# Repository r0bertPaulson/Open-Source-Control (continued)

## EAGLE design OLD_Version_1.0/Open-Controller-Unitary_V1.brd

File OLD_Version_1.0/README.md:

DO NOT USE THIS DESIGN. PROTOTYPE HAS NOT BEEN MADE OR TESTED. FOR REFERENCE ONLY. 

Please Use Version 2.1+

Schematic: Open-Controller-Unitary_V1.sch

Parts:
C1, C2: DNI; C0603
C3, C6, C9, C10, C14, C15, C17, C18, C19, C20, C22, C79, C93, C97: 0.1uF, 6.3V; C0402
C4: 330pF, DNI; C0805
C7, C12: 18pF, 50V; C0402
C8: 1nF; C0402
C11: 220uF, 6.3V; B/3528-21R
C13: 2.2uF, 6.3V; C0402
C16, C21: 10uF, 10V; C0805
C41, C44: 10uF, 16V; C0805
C42, C43, C45: 0.1uF, 16V; C0402
C46, C95, C96: 4.7uF; 1206
C85, C87, C88: 2200pF, 6.3V; C0402
C94: 1mF; CPOL-RADIAL-5MM-10MM
C111, C121, C131, C141, C151, C161: 1uF; C0805
D1, D2, D9, D21, D22, D23, D24, D25: LTST-C191KFKT; EIA-STD
D3: S1D; SMA
D4, D5, D6, D7, D8: LTST-C191KGKT; EIA-STD
D10, D11: SMBJ7.0CA; SMBJ
D13: B550C-13-F; SMC
D14, D15: SMBJ12CA; SMBJ
D16, D17: MBR0520LT; SOD123
EC30, EC31, EC34: 0.1uF, 6.3V; C0402
EC32: 10uF, 10V; C0805
EC33: 1uF, 10V; C0402
EC35: 470pF, 6.3V; C0402
EC36, EC37, EC38, EC39: 15pF, DNI; C0402
EC40: 0.022uF, 10V; C0402
EC41, EC42: 30pF, 50V; C0402
ER98, ER99, ER100, ER105: 1.5K, 1%; R0402
ER101, ER102, ER103, ER104, ER120, ER129: 10K, 1%; R0402
ER106, ER107, ER108, ER109: 49.9, 1%; R0402
ER110, ER111, ER112, ER113, ER114, ER116, ER118, ER119, ER123, ER124: 100, 1%; R0402
ER115, ER117: 470, 1%; R0402
ER122, ER126: 0, 1%; R0402
ER125: 1M, 1%, DNI; R0402
ER127: 10, 1%; R0402
ER128: 12.1K, 1%; R0402
F1: 4A Fuse; F1206W
F3, F4: MICROSMD010F-2; FUS_MICROSMD010F_TYCO
FB7: 150ohm, 800mA; C0805
FUD1, FUD2, FUD3, FUD4, FUD5, FUD6: FIDUCIAL; FIDUCIAL_40MIL
G1: CR2032V
IC1: LM2596S; TO263-5
IC2: ULN2003AD; SO16
IC3: L7824CT; 78XXL
IC4, IC5: 74HC165D; SO16
J1, J2, J6, J11, J12, J13, J21, J22, J23, J31, J32, J33, J41, J42, J43, J51, J52, J53, J61, J62, J63: 826646-2; H2-2.54
J3: 6p-2.54; H6-2.54
J4: CTI-JTAG
J7, J8: TH-2X5; H2X5-2.54
K1, K2, K3, K4, K5: JS1-24V-F; JS-M
L2: MSS1260
L3: 78253/55MVC-R; IND_78253_MC
MGT1, MGT2, MGT3, MGT4: MOUNTING_HOLE
Q1: MMBT2907; SOT23-BEC
R1, R3, R20, R42, R43, R44, R45, R46, R47, R48, R49, R50, R51, R52, R86, R87, R88, R89, R90, R91, R92, R160, R161, R171, R172, R173, R174, R175, R281, R282, R283, R284, R285, R286, R287, R288, R291, R292, R293, R294: 10K, 1%; R0402
R2, R9, R12, R13, R24, R26, R35, R36, R37, R38, R95, R96: 1.5K, 1%; R0402
R4, R5, R11, R19, R25, R28, R29, R30, R33: 0, 1%; R0402
R6, R54, R64, R65, R66, R70, R72, R73, R74, R75, R76, R77, R78, R79, R80, R84, R85: 100K, 1%, DNI; R0402
R8: 1K, 1%; R0402
R10: 0, 1%; R0805
R15: 40.2K, 1%; R0402
R17: 1.00K, 1%; R0805
R18, R22, R39, R40, R41: 4.75K, 1%; R0402
R21: 499; R0402
R27, R53, R55, R56, R57, R58, R59, R60, R61, R62, R63, R67, R68, R71, R81, R82, R83, R158: 100K, 1%; R0402
R31: 22, 1%; R0402
R32: 1M, 1%; R0402
R34: .1, 0805; R0805
R69: 100, 1%; R0402
R93: 3.09K, 1%; R0805
R94: 100, 5% DNI; R0805
R181, R182, R183, R184, R185, R186: 47V 200A; CT/CN1206
R211, R221, R231, R241, R251, R261: 80, 0.1%; 0309/12
R212, R214, R222, R224, R232, R234, R242, R244, R252, R254, R262, R264: 10K, 1%; R0805
R213, R223, R233, R243, R253, R263: 2K, 1%; R0805
RTC1: DS3231M; SO08
S1, S2: KMR231GLFS; SW4SMD_63X161LS
S11, S12: P101
S13: DS04; DS-04
TP1, TP2, TP3, TP4, TP12, TP13, TP14, TP15, TP16, TP21, TP22, TP23, TP24, TP27, TP28, TP29, TP30: TPB0,65; TP_B0,65
TP5, TP6, TP7, TP8, TP9, TP10, TP26: TESTPAD/W_HOLE_1X1
U1: OSD3358-512M-BSM; OSD335X-BGA-256
U2: TPD4S012_DRY_6_P1_M; DRY6
U3: SN74LVC1G07_DCK_5; DCK5
U4: APX811SOT; SOT143-R
U5: TLVH431; SOT23-3
U6: SN74LVC2G241_DCU_8; DCU8
U7: EMMC04G-S100-B08U; MICRON_EMMC_153
U8: LAN8710; LAN8710A-QFN32
U16: AT97SC3205T-G3M4400B; QFN32-0.4-4X4MM
U21: S25FL127S; W-PDFN-8
U25: ISO3086TDW; DW16
U26: LP2985A-33DBVR; DBV5
U27: TCAN1051HV; BEAGLEBONE_BLUE_D8
U$3, U$5, U$6: MCP6002SMT; SOIC8
U$4: MCP6001; SOT23-5
X1: 10118192-0001LF; 10118192-0001LF(MICRO-USB-B-AMPHENOL-FCI)
X2: MC2
X3: DM3BT-DSF-PEJS
X4: J0011D01BNL; SI-50170
X7: MSTBA2
X8: MC10
X9, X10, X11: MC4
X12: MC3
X13: MSTBA3
Y2: 7A-24.000MAAJ-T; CRYSTAL-TXC-7A
Y7: 7A-25.000MAAE-T; CRYSTAL-TXC-7A

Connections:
1P8V_REF: R212.2, R222.2, R232.2, R242.2, R252.2, R262.2, U$3.8 (V+), U$4.1 (OUT), U$4.4 (-IN), U$5.8 (V+), U$6.8 (V+)
5V_OUT: D13.C, IC1.2 (OUT), L2.1
24VAC: D3.A, F1.2
24VAC_IN: F1.1, X7.1
24VAC_UNREG: C94.+, C95.1, D3.C, IC1.1 (IN), IC3.IN
24VDC_AUX: D2.1 (A), D21.1 (A), D22.1 (A), D23.1 (A), D24.1 (A), D25.1 (A), IC2.9 (CD+), IC3.OUT, K1.1, K2.1, K3.1, K4.1, K5.1, X2.1, X2.2
AGND: C8.2, C9.2, C10.2, C111.2, C121.2, C131.2, C141.2, C151.2, C161.2, R25.2, R211.1, R213.2, R221.1, R223.2, R231.1, R233.2, R241.1, R243.2, R251.1, R253.2, R261.1, R263.2, U1.A9 (AGND_ADC), U$3.4 (V-), U$4.2 (V-), U$5.4 (V-), U$6.4 (V-), X9.2, X9.4, X10.2, X10.4, X11.2, X11.4
AIN0: U1.A8 (AIN0)
AIN1: U1.B8 (AIN1), U$3.1 (OUT), U$3.2 (-IN)
AIN2: U1.B6 (AIN2), U$3.6 (-IN), U$3.7 (OUT)
AIN3: U1.C6 (AIN3), U$5.1 (OUT), U$5.2 (-IN)
AIN4: U1.C7 (AIN4), U$5.6 (-IN), U$5.7 (OUT)
AIN5: U1.C8 (AIN5), U$6.1 (OUT), U$6.2 (-IN)
AIN6: U1.C9 (AIN6), U$6.6 (-IN), U$6.7 (OUT)
AIN7: U1.D6 (PMIC_MUX_OUT), U1.D7 (AIN7)
B03_NO: K3.NO (S), X8.6
BAT_SENSE: TP6.P$1, U1.N7 (PMIC_BAT_SENSE)
BO1_C: K1.C, X8.9
BO1_NO: K1.NO (S), X8.10
BO2_C: K2.C, X8.7
BO2_NO: K2.NO (S), X8.8
BO3_C: K3.C, X8.5
BO4_C: K4.C, X8.3
BO4_NO: K4.NO (S), X8.4
BO5_C: K5.C, X8.1
BO5_NO: K5.NO (S), X8.2
B_UART0_RX: J3.4, R27.2, U6.2 (1A)
B_UART0_TX: J3.5, U6.3 (2Y)
CGND: D10.A, D11.A, MGT1.P$1, MGT2.P$1, MGT3.P$1, MGT4.P$1, R34.2, R181.2, R182.2, R183.2, R184.2, R185.2, R186.2, X1.CGND1 (SGND1), X1.CGND2 (SGND2), X1.CGND3 (SGND3), X1.CGND4 (SGND4), X1.CGND5 (SGND5), X1.CGND6 (SGND6), X3.CGND1, X3.CGND2, X3.CGND3, X3.CGND4, X3.CGND5, X3.CGND6, X4.S1 (SHD1), X4.S2 (SHD2), X12.1
CLKOUT2: C2.2, J4.18 (EMU3), U1.B4 (XDMA_EVENT_INTR1)
CRS: ER124.1, U8.14 (CRS)
EEPROM_WP: J1.1, U1.M2 (EEPROM_WP)
EHRPWM1A: U1.P12 (GPMC_A2)
EHRPWM1B: U1.T13 (GPMC_A3)
EHRPWM2A: U1.T4 (GPMC_AD8)
EHRPWM2B: U1.P5 (GPMC_AD9)
EMMC_RSTN: R19.2, R52.1, U7.K5 (RST#)
EMMC_VCCI: C13.2, U7.C2 (VDDI)
GND: C1.1, C2.1, C3.2, C6.1, C11.-, C13.1, C14.2, C15.2, C16.1, C17.1, C18.1, C19.1, C20.1, C21.2, C22.2, C41.2, C42.2, C79.2, C85.2, C87.2, C88.2, C93.2, C94.-, C95.2, C96.2, C97.2, D13.A, EC30.2, EC31.2, EC32.2, EC33.2, EC34.2, EC35.2, EC36.2, EC37.2, EC38.2, EC39.2, EC40.2, EC41.2, EC42.2, ER101.2, ER102.2, ER103.2, ER104.2, ER115.1, ER117.1, ER120.1, ER128.1, ER129.2, G1.-, IC1.3 (GND), IC1.5 (EN), IC1.6 (GND), IC2.8 (GND), IC3.GND, IC4.8 (GND), IC4.15 (INH), IC5.3 (E), IC5.4 (F), IC5.5 (G), IC5.6 (H), IC5.8 (GND), IC5.15 (INH), J1.2, J2.2, J3.1, J4.4 (TDIS), J4.8 (GND1), J4.10 (GND2), J4.12 (GND3), J4.16 (GND4), J4.20 (GND5), J6.2, R1.2, R2.2, R3.2, R6.1, R9.2, R17.1, R18.1, R26.2, R27.1, R34.1, R35.2, R36.2, R37.2, R38.2, R39.1, R53.1, R54.1, R55.1, R56.1, R57.1, R58.1, R59.1, R60.1, R61.1, R62.1, R63.1, R64.1, R65.1, R66.1, R67.1, R68.1, R158.2, R281.1, R282.1, R283.1, R284.1, R285.1, R286.1, R287.1, R288.1, R291.1, R292.1, R293.1, R294.1, S1.2, S1.4, S2.1, S2.3, TP8.P$1, U1.D8 (DGND), U1.D9 (DGND), U1.E5 (DGND), U1.E6 (DGND), U1.E7 (DGND), U1.E8 (DGND), U1.E9 (DGND), U1.E10 (DGND), U1.E11 (DGND), U1.E12 (DGND), U1.F5 (DGND), U1.F12 (DGND), U1.G5 (DGND), U1.G12 (DGND), U1.H4 (DGND), U1.H5 (DGND), U1.H12 (DGND), U1.H13 (DGND), U1.J4 (DGND), U1.J5 (DGND), U1.J12 (DGND), U1.J13 (DGND), U1.K5 (DGND), U1.K12 (DGND), U1.L5 (DGND), U1.L12 (DGND), U1.M5 (DGND), U1.M6 (DGND), U1.M7 (DGND), U1.M8 (DGND), U1.M9 (DGND), U1.M10 (DGND), U1.M11 (DGND), U1.M12 (DGND), U1.N8 (DGND), U1.N9 (DGND), U2.4 (GND), U3.3 (GND), U4.1 (GND), U6.1 (*1OE), U6.4 (GND), U7.C4 (VSSQ1), U7.E7 (VSS1), U7.G5 (VSS2), U7.H10 (VSS3), U7.K8 (VSS4), U7.N2 (VSSQ2), U7.N5 (VSSQ3), U7.P4 (VSSQ4), U7.P6 (VSSQ5), U8.33 (GND_EP), U16.2 (GND), U16.5 (TESTL), U16.6 (XTAMPER), U16.9 (GND), U16.18 (PIRQ#), U16.19 (ATEST), U16.20 (TWI_WAKEUP#), U16.21 (ATEST), U16.23 (GND), U16.24 (ATEST), U16.32 (GND), U21.4 (VSS), U25.3 (GND1), U27.2 (GND), X1.GND, X3.6 (VSS), X3.GND, X4.8 (D_GND), X7.2
GPIO0_18: RTC1.3 (SQW), U1.J15 (USB0_DRVVBUS)
GPIO0_26: U1.R5 (GPMC_AD10)
GPIO0_27: U1.T5 (GPMC_AD11)
GPIO1_12: IC2.2 (I2), U1.P6 (GPMC_AD12)
GPIO1_13: IC2.3 (I3), U1.R6 (GPMC_AD13)
GPIO1_14: IC2.4 (I4), U1.T6 (GPMC_AD14)
GPIO1_15: IC2.5 (I5), U1.P7 (GPMC_AD15)
GPIO1_16: U1.T12 (GPMC_A0), U25.6 (!RE), U25.7 (DE)
GPIO1_28: U1.N14 (GPMC_BEN1)
GPIO1_29: U1.P3 (GPMC_CSN0)
GPIO2_1: U1.T7 (GPMC_CLK)
GPIO3_21: IC2.1 (I1), U1.C4 (MCASP0_AHCLKX)
HDMICLK_DISN: U1.T16 (GPMC_A11)
HDMI_INT: U1.T15 (GPMC_A9)
I2C0_SCL: R12.1, U1.C10 (I2C0_SCL), U1.D10 (PMIC_SCL), U16.29 (SM_CLK)
I2C0_SDA: R13.1, U1.C11 (I2C0_SDA), U1.D11 (PMIC_SDA), U16.30 (SM_DAT)
I2C2_SCL: R95.1, RTC1.8 (SCL), U1.A10 (UART1_RTSN)
I2C2_SDA: R96.1, RTC1.7 (SDA), U1.B10 (UART1_CTSN)
ISO_GND: C43.2, C44.2, C45.2, C46.2, D14.A, D15.A, L3.5, U25.9 (GND2_2), U25.15 (GND2), U26.2 (GND), X13.3
ISO_VIN: C44.1, C45.1, D16.C, D17.C, U26.1 (VIN), U26.3 (ON/!OFF)
JTAG_EMU0: J4.13 (EMU0), R40.1, U1.E2 (EMU0)
JTAG_EMU1: J4.14 (EMU1), R41.1, U1.E3 (EMU1)
JTAG_TCK: J4.9 (TCKRTN), J4.11 (TCK), U1.D1 (TCK)
JTAG_TDI: J4.3 (TDI), U1.C1 (TDI)
JTAG_TDO: J4.7 (TDO), U1.C2 (TDO)
JTAG_TMS: J4.1 (TMS), U1.D2 (TMS)
JTAG_TRSTN: J4.2 (TRSTN), R39.2, U1.D3 (TRSTN)
LCD_DATA0: J8.9, R68.2, R85.1, U1.G3 (LCD_DATA0)
LCD_DATA1: J8.10, R67.2, R84.1, U1.G2 (LCD_DATA1)
LCD_DATA2: J8.7, R66.2, R69.1, R83.1, U1.G1 (LCD_DATA2)
LCD_DATA3: J8.8, R65.2, R82.1, U1.H3 (LCD_DATA3)
LCD_DATA4: J8.5, R64.2, R81.1, U1.H2 (LCD_DATA4)
LCD_DATA5: J8.6, R63.2, R80.1, U1.H1 (LCD_DATA5)
LCD_DATA6: J8.3, R62.2, R79.1, U1.J3 (LCD_DATA6)
LCD_DATA7: J8.4, R61.2, R78.1, U1.J2 (LCD_DATA7)
LCD_DATA8: J8.1, R60.2, R77.1, U1.J1 (LCD_DATA8)
LCD_DATA9: J8.2, R59.2, R76.1, U1.K3 (LCD_DATA9)
LCD_DATA10: J7.10, R58.2, R75.1, U1.K2 (LCD_DATA10)
LCD_DATA11: J7.8, R57.2, R74.1, U1.K1 (LCD_DATA11)
LCD_DATA12: J7.9, R56.2, R73.1, U1.L3 (LCD_DATA12)
LCD_DATA13: J7.7, R55.2, R72.1, U1.L2 (LCD_DATA13)
LCD_DATA14: J7.5, R54.2, R71.1, U1.L1 (LCD_DATA14)
LCD_DATA15: J7.6, R53.2, R70.1, U1.M3 (LCD_DATA15)
LCD_DE: J7.4, R28.2
LCD_HSYNC: J7.3, R29.2
LCD_PCLK: J7.2, R31.2
LCD_VSYNC: J7.1, R30.2
LDO_PGOOD: TP22.TP, U1.N4 (PMIC_LDO_PGOOD), U1.N5 (RTC_PWRONRSTN)
MDIO_CLK: U1.D13 (MDC), U8.17 (MDC)
MDIO_DATA: ER105.2, U1.E13 (MDIO), U8.16 (MDIO)
MII1_COL: ER123.2, U1.F15 (MII1_COL)
MII1_CRS: ER124.2, U1.F14 (MII1_CRS)
MII1_RXCLK: ER116.2, U1.E16 (MII1_RX_CLK)
MII1_RXD0: ER113.2, U1.E14 (MII1_RXD0)
MII1_RXD1: ER112.2, U1.D16 (MII1_RXD1)
MII1_RXD2: ER111.2, U1.D15 (MII1_RXD2)
MII1_RXD3: ER110.2, U1.D14 (MII1_RXD3)
MII1_RXDV: ER114.2, U1.F16 (MII1_RX_DV)
MII1_RXERR: ER118.2, U1.E15 (MII1_RX_ER)
MII1_TXCLK: ER119.2, U1.H16 (MII1_TX_CLK)
MII1_TXD0: U1.H15 (MII1_TXD0), U8.22 (TXD0)
MII1_TXD1: U1.H14 (MII1_TXD1), U8.23 (TXD1)
MII1_TXD2: U1.G16 (MII1_TXD2), U8.24 (TXD2)
MII1_TXD3: U1.G15 (MII1_TXD3), U8.25 (TXD3)
MII1_TXEN: U1.G14 (MII1_TX_EN), U8.21 (TXEN)
MMC0_CD: J4.19 (EMU4), R92.1, U1.C14 (SPI0_CS1), X3.CD (CD#)
MMC0_CLK: R88.1, U1.B15 (MMC0_CLK), X3.5 (CLK)
MMC0_CMD: R87.1, U1.B16 (MMC0_CMD), X3.3 (CMD/DI)
MMC0_DAT0: R89.1, U1.A16 (MMC0_DAT0), X3.7 (DAT0/DO)
MMC0_DAT1: R90.1, U1.A15 (MMC0_DAT1), X3.8 (DAT1)
MMC0_DAT2: R86.1, U1.C16 (MMC0_DAT2), X3.1 (DAT2)
MMC0_DAT3: R91.1, U1.C15 (MMC0_DAT3), X3.2 (DAT3/CS)
MMC1_CLK: R51.1, U1.P2 (GPMC_CSN1), U7.M6 (CLK)
MMC1_CMD: R50.1, U1.P1 (GPMC_CSN2), U7.M5 (CMD)
MMC1_DAT0: R42.1, U1.R3 (GPMC_AD0), U7.A3 (DAT0)
MMC1_DAT1: R43.1, U1.R2 (GPMC_AD1), U7.A4 (DAT1)
MMC1_DAT2: R44.1, U1.R1 (GPMC_AD2), U7.A5 (DAT2)
MMC1_DAT3: R45.1, U1.T3 (GPMC_AD3), U7.B2 (DAT3)
MMC1_DAT4: R46.1, U1.T2 (GPMC_AD4), U7.B3 (DAT4)
MMC1_DAT5: R47.1, U1.T1 (GPMC_AD5), U7.B4 (DAT5)
MMC1_DAT6: R48.1, U1.P4 (GPMC_AD6), U7.B5 (DAT6)
MMC1_DAT7: R49.1, U1.R4 (GPMC_AD7), U7.B6 (DAT7)
MODE2: ER99.2, ER123.1, U8.15 (COL/CRS_DV/MODE2)
unnamed: R10.1, X1.VBUS
unnamed: D7.2 (C), R38.1
unnamed: J6.1, R69.2
unnamed: R8.2, U4.2 (RESET#)
unnamed: TP1.TP, U1.F4 (VDDS_DDR)
unnamed: D2.2 (C), R3.1
unnamed: D1.2 (C), R26.1
unnamed: R15.2, R20.1, U5.1 (REF)
unnamed: Q1.B, R21.1, U5.2 (CATHODE)
unnamed: D6.2 (C), R37.1
unnamed: D5.2 (C), R36.1
unnamed: J11.1, J12.1, R181.1, R214.1, X9.1
unnamed: D4.2 (C), R35.1
unnamed: D10.C, U27.7 (CANH), X12.3
unnamed: D11.C, U27.6 (CANL), X12.2
unnamed: TP2.TP, U1.G4 (VDD_CORE)
unnamed: TP3.TP, U1.F13 (VDD_MPU)
unnamed: TP4.TP, U1.G13 (VDDS_PLL)
unnamed: R4.1, U1.A4 (XDMA_EVENT_INTR0)
unnamed: R161.2, U21.3 (W#)
unnamed: J51.1, J52.1, R185.1, R254.1, X11.1
unnamed: R160.2, U21.7 (HOLD#)
unnamed: R19.1, U1.R13 (GPMC_A4)
unnamed: R11.1, S1.1, S1.3
unnamed: C151.1, J53.1, R254.2, U$6.3 (+IN)
unnamed: J51.2, R251.2
unnamed: R5.1, U3.4 (Y)
unnamed: J53.2, R253.1
unnamed: J52.2, R252.1
unnamed: R1.1, U1.M16 (RTC_KALDO_ENN)
unnamed: J61.1, J62.1, R186.1, R264.1, X11.3
unnamed: D8.2 (C), R2.1
unnamed: EC40.1, ER122.2, X4.4 (TCT), X4.5 (RCT)
unnamed: D21.2 (C), R171.1
unnamed: D23.2 (C), R173.1
unnamed: D22.2 (C), R172.1
unnamed: IC2.16 (O1), K1.2, R171.2
unnamed: IC2.15 (O2), K2.2, R172.2
unnamed: C161.1, J63.1, R264.2, U$6.5 (+IN)
unnamed: D24.2 (C), R174.1
unnamed: D25.2 (C), R175.1
unnamed: J11.2, R211.2
unnamed: J12.2, R212.1
unnamed: J61.2, R261.2
unnamed: J63.2, R263.1
unnamed: J62.2, R262.1
unnamed: IC2.13 (O4), K4.2, R174.2
unnamed: IC2.12 (O5), K5.2, R175.2
unnamed: IC2.14 (O3), K3.2, R173.2
unnamed: J13.2, R213.1
unnamed: J21.1, J22.1, R182.1, R224.1, X9.3
unnamed: C121.1, J23.1, R224.2, U$3.5 (+IN)
unnamed: G1.+, RTC1.6 (VBAT)
unnamed: IC4.6 (H), R288.2, S12.8
unnamed: C111.1, J13.1, R214.2, U$3.3 (+IN)
unnamed: J21.2, R221.2
unnamed: J23.2, R223.1
unnamed: J22.2, R222.1
unnamed: D9.2 (C), R9.1
unnamed: C4.1, R94.1
unnamed: J31.1, J32.1, R183.1, R234.1, X10.1
unnamed: C131.1, J33.1, R234.2, U$5.3 (+IN)
unnamed: J31.2, R231.2
unnamed: J33.2, R233.1
unnamed: R31.1, U1.F1 (LCD_PCLK)
unnamed: J32.2, R232.1
unnamed: R30.1, U1.F3 (LCD_VSYNC)
unnamed: J41.1, J42.1, R184.1, R244.1, X10.3
unnamed: C141.1, J43.1, R244.2, U$5.5 (+IN)
unnamed: J41.2, R241.2
unnamed: J43.2, R243.1
unnamed: C4.2, IC1.4 (FB), R17.2, R93.1
unnamed: J42.2, R242.1
unnamed: D14.C, F3.2, U25.11 (Y), U25.14 (A)
unnamed: D15.C, F4.2, U25.12 (Z), U25.13 (B)
unnamed: F3.1, X13.1
unnamed: F4.1, X13.2
unnamed: R29.1, U1.F2 (LCD_HSYNC)
unnamed: C43.1, C46.1, U25.16 (VCC2), U26.5 (VOUT)
unnamed: R28.1, U1.E1 (LCD_AC_BIAS_EN)
unnamed: D16.A, L3.6
unnamed: D17.A, L3.4
unnamed: L3.1, U25.1 (D1)
unnamed: L3.3, U25.2 (D2)
unnamed: IC4.5 (G), R287.2, S12.4
unnamed: IC4.4 (F), R286.2, S12.2
unnamed: IC4.3 (E), R285.2, S12.1
unnamed: IC4.14 (D), R284.2, S11.8
unnamed: IC4.13 (C), R283.2, S11.4
unnamed: IC4.12 (B), R282.2, S11.2
unnamed: IC4.11 (A), R281.2, S11.1
unnamed: IC5.11 (A), R291.2, S13.8
unnamed: IC5.12 (B), R292.2, S13.7
unnamed: IC5.13 (C), R293.2, S13.6
unnamed: IC5.14 (D), R294.2, S13.5
unnamed: IC4.10 (SER), IC5.9 (QH)
unnamed: ER126.1, U8.5 (XTAL1/CLKIN)
unnamed: EC42.1, ER125.2, ER126.2, Y7.P$2 (2)
unnamed: EC41.1, ER127.2, Y7.P$1 (1)
unnamed: ER125.1, ER127.1, U8.4 (XTAL2)
unnamed: ER128.2, U8.32 (RBIAS)
unnamed: ER129.1, U8.18 (NINT/TXER/TXD4)
unnamed: ER120.2, U8.2 (LED2/!INTSEL), X4.A1 (YELA)
unnamed: U8.3 (LED1/REGOFF), X4.C2 (GRNA)
unnamed: EC33.1, EC35.1, U8.6 (VDDCR)
unnamed: ER115.2, X4.C1 (YELC)
unnamed: ER117.2, X4.A2 (GRNC)
OSC0_GND: C7.2, C12.2, U1.N15 (OSC0_GND)
OSC0_IN: C12.1, R32.2, U1.P16 (OSC0_IN), Y2.P$2 (2)
OSC0_OUT: C7.1, R32.1, U1.N16 (OSC0_OUT), Y2.P$1 (1)
OSC1_GND: RTC1.5 (GND), U1.B5 (OSC1_GND)
OSC1_IN: R24.2, RTC1.1 (32KHZ), U1.A6 (OSC1_IN)
OSC1_OUT: U1.A5 (OSC1_OUT)
PMIC_INT: TP24.TP, U1.D4 (EXTINTN), U1.E4 (PMIC_NINT)
PMIC_MUX_IN: R18.2, R22.1, U1.N13 (PMIC_MUX_IN)
PMIC_NRESET: J2.1, U1.M13 (PMIC_NRESET)
PMIC_NWAKEUP: TP23.TP, U1.L4 (PMIC_NWAKEUP), U1.M4 (EXT_WAKEUP)
PMIC_PGOOD: U1.N12 (PMIC_PGOOD), U1.P11 (PWRONRSTN), U3.2 (A)
PWR_BUT: S2.2, S2.4, U1.T11 (PMIC_PB_IN)
PWR_EN: TP21.TP, U1.N10 (PMIC_POWER_EN), U1.N11 (PMIC_PWR_EN)
RESET: R5.2, R11.2, U4.3 (MR#)
RTC_RST: RTC1.4 (RST), U1.R12 (GPMC_A1)
RXD0: ER98.2, ER113.1, U8.11 (RXD0/MODE0)
RXD1: ER100.2, ER112.1, U8.10 (RXD1/MODE1)
RXD2: ER103.1, ER111.1, U8.9 (RXD2/RMIISEL)
RXD3: ER102.1, ER110.1, U8.8 (RXD3/PHYAD2)
RX_CLK: ER104.1, ER116.1, U8.7 (RXCLK/PHYAD1)
RX_DV: ER114.1, U8.26 (RXDV)
RX_ERR: ER101.1, ER118.1, U8.13 (RXER/RXD4/PHYAD0)
RX_N: EC37.1, ER107.2, U8.30 (RXN), X4.2 (RXN)
RX_P: EC36.1, ER106.2, U8.31 (RXP), X4.1 (RXP)
SPI0_CS0: R158.1, TP30.TP, U1.A14 (SPI0_CS0), U21.1 (S#)
SPI0_D0(MISO): TP29.TP, U1.B13 (SPI0_D0), U21.2 (DQ1)
SPI0_D1(MOSI): TP28.TP, U1.B14 (SPI0_D1), U21.5 (DQ0)
SPI0_SCLK: TP27.TP, U1.A13 (SPI0_SCLK), U21.6 (C)
SPI1_CS0: IC4.1 (SH/!LD), IC5.1 (SH/!LD), U1.B1 (MCASP0_AHCLKR)
SPI1_D0: IC4.9 (QH), U1.A2 (MCASP0_FSX)
SPI1_D1: U1.B2 (MCASP0_AXR0)
SPI1_SCLK: IC4.2 (CLK), IC5.2 (CLK), U1.A1 (MCASP0_ACLKX)
SYS_ADC_1P8V: C10.1, R33.2, U1.A7 (SYS_ADC_1P8V), U$4.3 (+IN)
SYS_RESETN: C14.1, J4.15 (SRST), R6.2, R8.1, TP26.P$1, U1.R11 (WARMRSTN), U8.19 (!RST), U16.17 (LRESET#)
SYS_RTC_1P8V: Q1.C, R15.1, TP14.TP, U1.K11 (SYS_RTC_1P8V), U1.L11 (SYS_RTC_1P8V), U3.5 (VCC), U5.3 (ANODE)
SYS_VDD1_3P3V: C6.2, C15.1, C16.2, C17.2, C18.2, C19.2, C20.2, C21.1, C22.1, C41.1, C42.1, C79.1, C85.1, C87.1, C88.1, C93.1, C97.1, EC34.1, ER98.1, ER99.1, ER100.1, ER105.1, FB7.1, IC4.16 (VCC), IC5.16 (VCC), J4.5 (TVDD), L3.2, R12.2, R13.2, R22.2, R24.1, R40.2, R41.2, R42.2, R43.2, R44.2, R45.2, R46.2, R47.2, R48.2, R49.2, R50.2, R51.2, R52.2, R70.2, R71.2, R72.2, R73.2, R74.2, R75.2, R76.2, R77.2, R78.2, R79.2, R80.2, R81.2, R82.2, R83.2, R84.2, R85.2, R86.2, R87.2, R88.2, R89.2, R90.2, R91.2, R92.2, R95.2, R96.2, R160.1, R161.1, RTC1.2 (VCC), S11.C, S12.C, S13.1, S13.2, S13.3, S13.4, TP12.TP, U1.F6 (SYS_VDD1_3P3V), U1.F7 (SYS_VDD1_3P3V), U1.G6 (SYS_VDD1_3P3V), U1.G7 (SYS_VDD1_3P3V), U4.4 (VCC), U6.7 (2OE), U6.8 (VCC), U7.C6 (VCCQ1), U7.E6 (VCC1), U7.F5 (VCC2), U7.J10 (VCC3), U7.K9 (VCC4), U7.M4 (VCCQ2), U7.N4 (VCCQ3), U7.P3 (VCCQ4), U7.P5 (VCCQ5), U8.12 (VDDIO), U16.1 (VCC), U16.8 (VCC), U16.22 (VCC), U21.8 (VCC), U25.4 (VCC1), U27.3 (VCC), U$4.5 (V+), X3.4 (VDD)
SYS_VDD2_3P3V: D1.1 (A), TP13.TP, U1.F11 (SYS_VDD2_3P3V), U1.G11 (SYS_VDD2_3P3V)
SYS_VDD3_3P3V: Q1.E, R20.2, R21.2, TP16.TP, U1.F8 (SYS_VDD3_3P3V), U1.F9 (VDDSHV4), U1.G8 (SYS_VDD3_3P3V), U1.G9 (VDDSHV5), U1.H7 (SYS_VDD3_3P3V), U1.H8 (SYS_VDD3_3P3V), U1.H9 (VDDSHV6), U1.J7 (SYS_VDD3_3P3V), U1.J8 (SYS_VDD3_3P3V), U1.J9 (VDDSHV1), U1.K8 (SYS_VDD3_3P3V), U1.K9 (VDDSHV2), U1.L8 (SYS_VDD3_3P3V), U1.L9 (VDDSHV3)
SYS_VDD_1P8V: TP15.TP, U1.F10 (SYS_VDD_1P8V), U1.G10 (SYS_VDD_1P8V), U1.H10 (SYS_VDD_1P8V), U1.H11 (SYS_VDD_1P8V), U1.J10 (SYS_VDD_1P8V), U1.J11 (SYS_VDD_1P8V), U1.K10 (SYS_VDD_1P8V), U1.L10 (SYS_VDD_1P8V)
SYS_VOUT: U1.K6 (SYS_VOUT), U1.K7 (SYS_VOUT), U1.L6 (SYS_VOUT), U1.L7 (SYS_VOUT)
TEMP_SENSE: TP7.P$1, U1.N6 (PMIC_TS)
TIMER4: U1.M1 (GPMC_ADVN_ALE)
TIMER5: U1.N3 (GPMC_BEN0_CLE)
TIMER6: U1.N2 (GPMC_WEN)
TIMER7: U1.N1 (GPMC_OEN_REN)
TPM_GPIO0: U1.B3 (MCASP0_FSR), U16.12 (GPIO)
TPM_GPIO1: TP9.P$1, U1.C12 (UART0_CTSN), U16.3 (GPIO-EXPRESS-00)
TPM_GPIO2: TP10.P$1, U1.C13 (UART0_RTSN), U16.4 (PP/GPIO)
TX_CLK: ER119.1, U8.20 (TXCLK)
TX_N: EC39.1, ER109.2, U8.28 (TXN), X4.6 (TXN)
TX_P: EC38.1, ER108.2, U8.29 (TXP), X4.3 (TXP)
UART0_RX: U1.A12 (UART0_RXD), U6.6 (1Y)
UART0_TX: U1.B12 (UART0_TXD), U6.5 (2A)
UART1_RXD: U1.A11 (UART1_RXD), U27.4 (RXD)
UART1_TXD: U1.B11 (UART1_TXD), U27.1 (TXD)
UART4_RXD: D9.1 (A), U1.P15 (GPMC_WAIT0), U25.5 (R)
UART4_TXD: D8.1 (A), U1.R16 (GPMC_WPN), U25.8 (D)
USB0_DM: U1.K16 (USB0_DM), U2.1 (D-), X1.D-
USB0_DP: U1.K15 (USB0_DP), U2.2 (D+), X1.D+
USB0_ID: U1.K14 (USB0_ID), U2.3 (ID), X1.ID
USB1_OCN: U1.R15 (GPMC_A10)
USR0: D7.1 (A), U1.P13 (GPMC_A5)
USR1: D6.1 (A), U1.T14 (GPMC_A6)
USR2: D5.1 (A), U1.R14 (GPMC_A7)
USR3: D4.1 (A), U1.P14 (GPMC_A8)
VDD_5V: C11.+, C96.1, L2.2, R93.2, R94.2, U1.P10 (VIN_AC), U1.R10 (VIN_AC), U1.T10 (VIN_AC)
VDD_BAT: TP5.P$1, U1.P8 (VIN_BAT), U1.R8 (VIN_BAT), U1.T8 (VIN_BAT)
VDD_ETH_PHY: EC30.1, EC31.1, EC32.1, ER106.1, ER107.1, ER108.1, ER109.1, ER122.1, FB7.2, U8.1 (VDD2A), U8.27 (VDD1A)
VDD_USB_5V: C3.1, R10.2, U1.J16 (USB0_VBUS), U1.P9 (VIN_USB), U1.R9 (VIN_USB), U1.T9 (VIN_USB), U2.6 (VBUS)
VIO: U27.5 (VIO)
VREFN: R25.1, U1.B9 (VREFN)
VREFP: C8.1, C9.1, R33.1, U1.B7 (VREFP)
XDMA_EVENT_INTR0: C1.2, J4.17 (EMU2), R4.2

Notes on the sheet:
Power & Reset
Clocks, Analog & USB
SiP Interfaces
Boot configuration
eMMC
LCD Headers
Micro SD card slot
User LEDs
JTAG Header
Beaglebone Ethernet
USB Client
SiP GND & Misc
1/12
3/12
2/12
4/12
5/12
6/12
9/12
8/12
7/12
Mounting Holes
Fiducials
User Config Switches
External Real Time Clk
TPM
Secure NOR Boot Flash
Notes
12/12
11/12
10/12
Power Supply
Relay Outputs
Universal Inputs
RS-485 Interface
CAN Interface

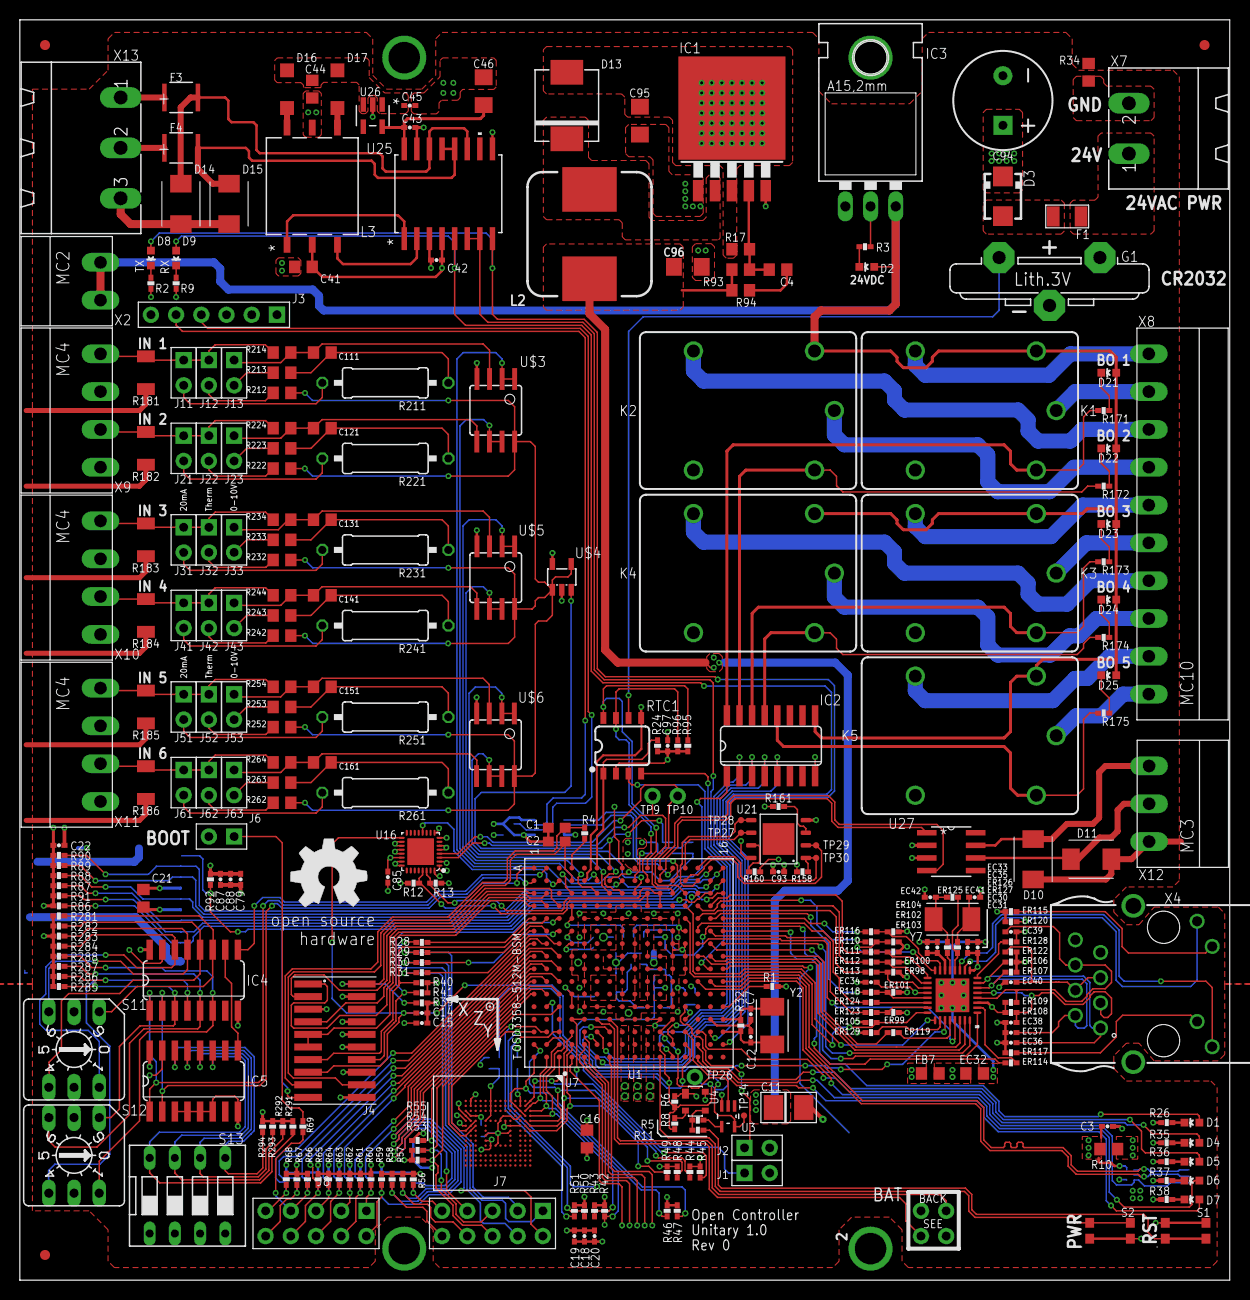
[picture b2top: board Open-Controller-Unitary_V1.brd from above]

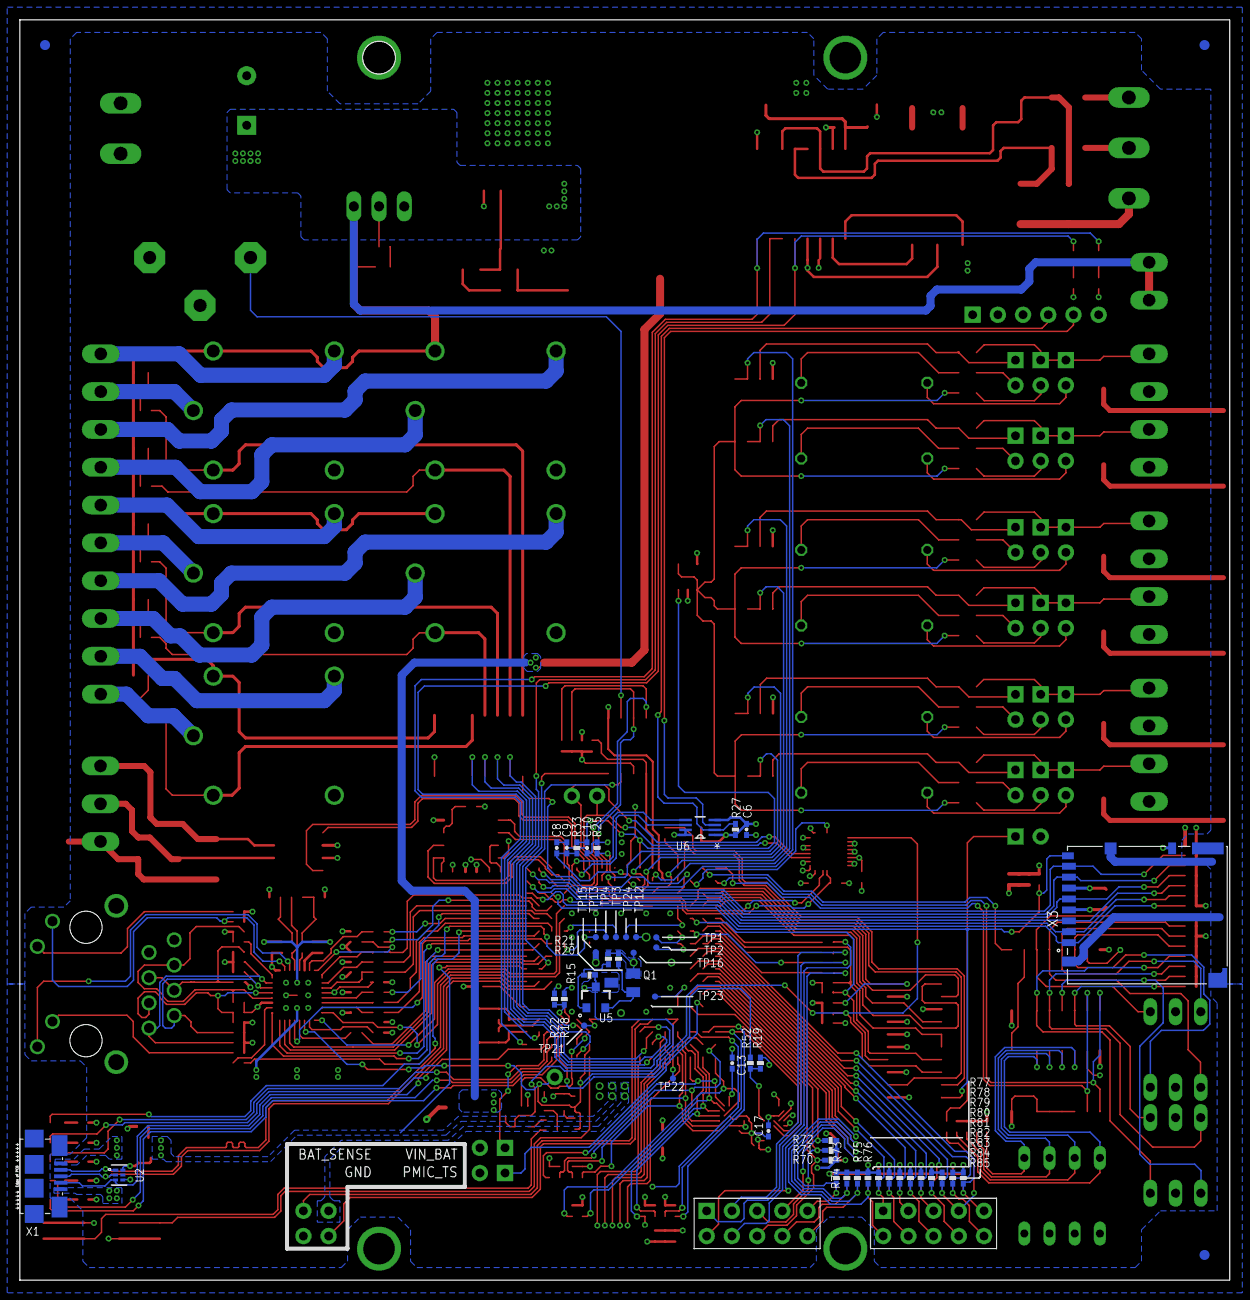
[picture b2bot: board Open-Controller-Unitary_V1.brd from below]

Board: 4 copper layers, 121.9 x 127.0 mm, 364 parts (53 on the bottom side), 282 nets.

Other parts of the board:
U$2: XYZ-LABEL
U$8: OSHW_8MM

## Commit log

2019-12-04 v2.1 Prototype - Final
2020-10-21 Add files via upload
    adding PRU UART option
2024-06-23 Add files via upload
    Fixed CAN1_TXD CAN1_RXD criss-crossed
2024-06-24 Added 6th B-output BO_6
    Added 6th B-output BO_6 to expansion header. Now a total of 6 relay outputs are possible
2025-02-13 Create uEnv.txt
    If you use a Beagle Image (this one is for image 2023-10-07), these overlays will enable all the correct peripherals
